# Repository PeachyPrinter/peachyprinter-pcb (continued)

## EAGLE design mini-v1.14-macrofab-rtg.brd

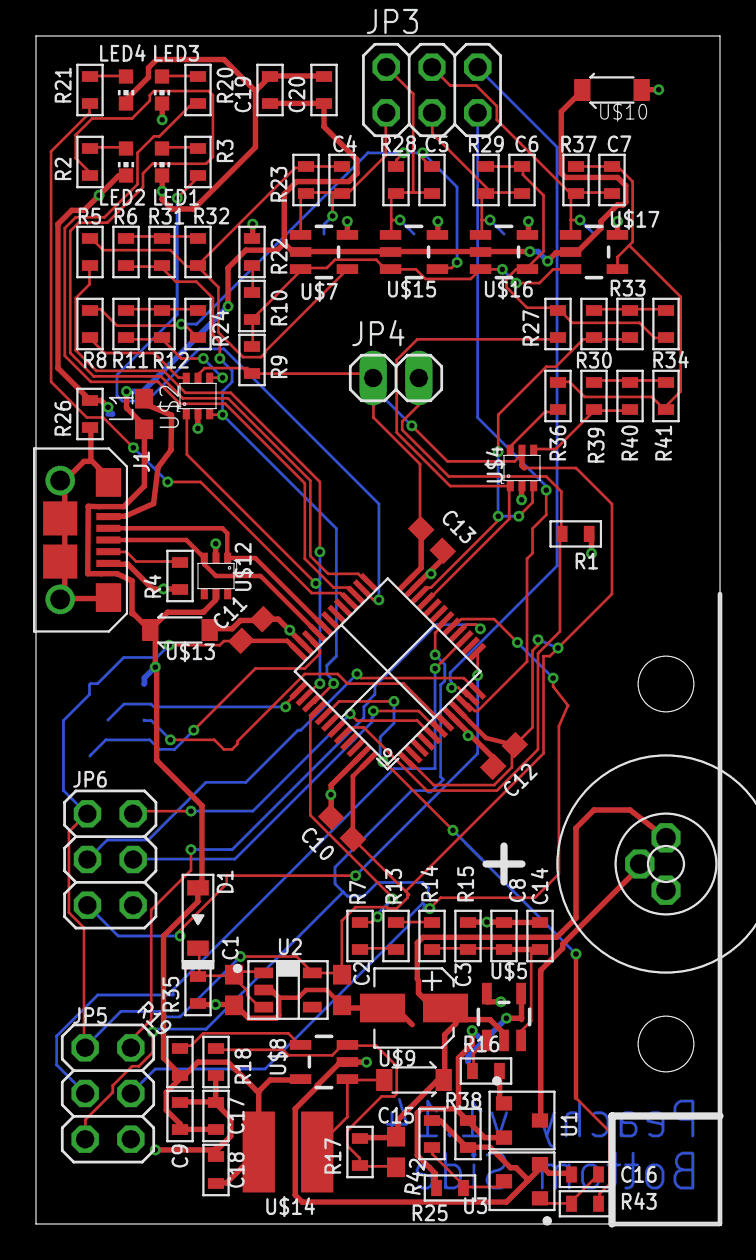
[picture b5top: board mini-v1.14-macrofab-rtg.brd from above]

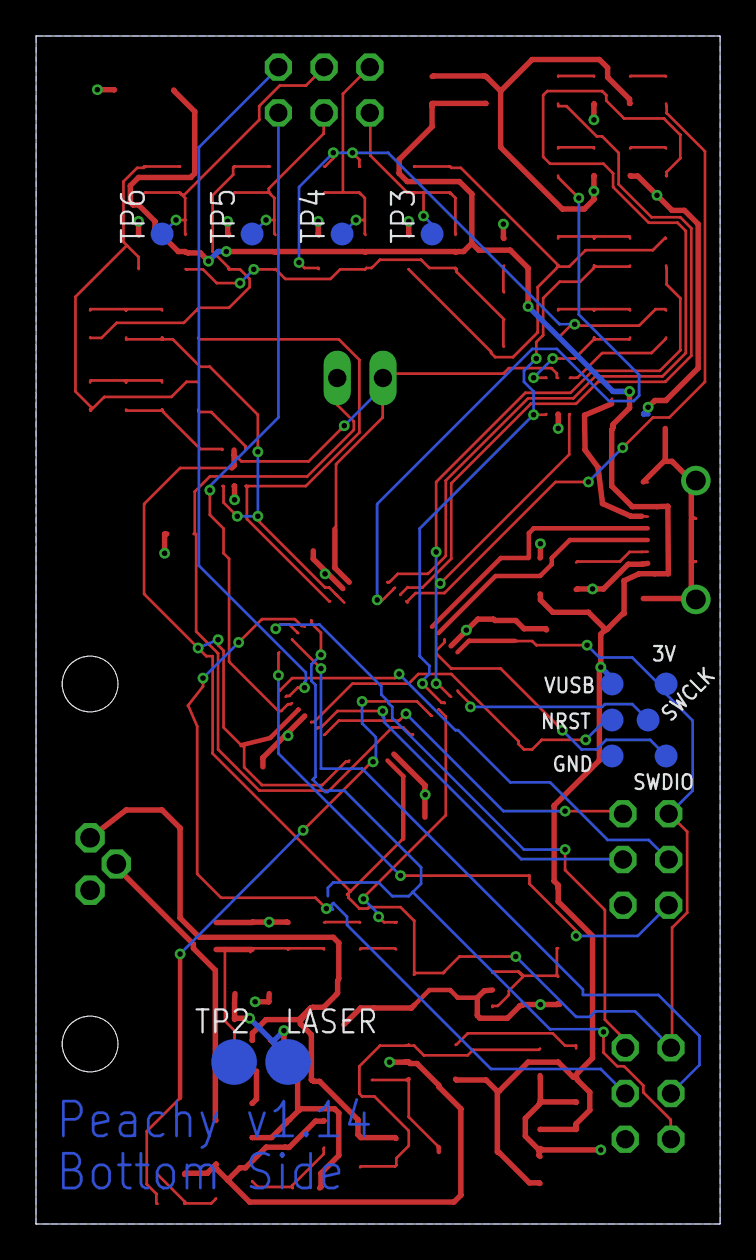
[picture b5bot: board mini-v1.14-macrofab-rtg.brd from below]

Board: 2 copper layers, 38.0 x 66.0 mm, 104 parts (12 on the bottom side), 68 nets.

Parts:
3V: TPB1,27; B1,27
C1, C2, C9, C17, C19: 1uF; C0603
C3: 10uF; CP4MM
C4, C5, C6, C7: 100n; C0603
C8, C10, C11, C12, C13, C14, C16, C18, C20: 0.1uF; C0603
C15: 560pF/50V; C0603
D1: BAT42; SOD-123
GND: TPB1,27; B1,27
J1: MICROUSB-RIGHT
JP3, JP5, JP6: 2X03
JP4: 1X02
L1: ferrite; C0603
LASER: TPB2,54; B2,54
LD1: SCOTT_LASERDIODELD3; SCOTT_LASERDIODE3
LED1, LED2, LED3, LED4: CHIP-LED0603
NRST: TPB1,27; B1,27
R1, R18: 13k3; R0603
R2, R3, R5, R7, R8, R9, R10, R20, R21, R22, R23, R27, R28, R29, R36, R37: 2k; R0603
R4: 100k; R0603
R6, R11, R12, R19, R30, R31, R33, R35, R39, R40: 825k; R0603
R13, R14, R15, R38, R43: 1k69; R0603
R16, R25: 10; R0603
R17: 63k4; R0603
R24, R26, R32, R34, R41: 604k; R0603
R42: N/C; R0603
SWCLK: TPB1,27; B1,27
SWDIO: TPB1,27; B1,27
TP2: GND; B2,54
TP3, TP4, TP5, TP6: TPB1,27; B1,27
U1, U3: BSS138; SOT-23-3
U2: TLV70233PDBVR; SOT-23-5
U$1: STM32F042C6T6-LQFP48; LQFP48
U$2, U$4: NC7WZ14P6X; SC70-6
U$5, U$7, U$15, U$16, U$17: LMC7101; SOT23-5
U$8: LMR62014; SOT23-5
U$9: MBR0520; SOD123
U$10, U$13: SMF6.0A; SOD123
U$12: SP3002-04JTG; SC70-6
U$14: SDR0403-100ML; SDR0403
VUSB: TPB1,27; B1,27

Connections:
2V2: R9.P$1, R10.P$2, U$7.3, U$15.3, U$16.3, U$17.3
3V: 3V.TP, C2.2, C10.1, C11.1, C12.1, C13.1, JP4.1, JP5.1, JP6.1, R9.P$2, U2.P$5, U$1.P1, U$1.P9, U$1.P24, U$1.P36, U$1.P48, U$2.P5, U$4.P5
6V: C3.P$1, C15.2, LD1.P$1, R17.P$2, U$5.2, U$9.CATHODE
ADC0: JP3.5, U$1.P10
ADC1: JP3.6, U$1.P11
ADC2: JP6.3, U$1.P12
ADC3: JP6.5, U$1.P13
BOOT0: JP4.2, R1.P$2, U$1.P44
COARSE1: R8.P$1, U$2.P6
FINE1: R11.P$1, R12.P$1, U$2.P4
FINE3: R39.P$1, R40.P$1, U$4.P4
GND: C1.2, C2.1, C3.P$2, C8.P$2, C9.P$2, C10.2, C11.2, C12.2, C13.2, C14.P$2, C16.P$2, C17.P$2, C18.P$2, C19.P$2, C20.P$2, GND.TP, J1.5, JP5.6, JP6.6, LED1.C, LED2.C, LED3.C, LED4.C, R1.P$1, R4.P$1, R15.P$2, R18.P$1, R22.P$1, R26.P$2, R35.P$1, R38.P$1, R42.P$1, TP2.TP, U2.P$2, U3.P$2, U$1.P8, U$1.P23, U$1.P35, U$1.P47, U$2.P2, U$4.P2, U$5.5, U$7.5, U$8.2, U$10.ANODE, U$12.P2, U$13.ANODE, U$15.5, U$16.5, U$17.5
LASER_EN: R43.P$2, U$1.P41
LASER_PWM_IN: R7.P$2, U$1.P40
MISO: JP5.2, U$1.P16
MOSI: JP5.4, U$1.P17
unnamed: R25.P$1, R42.P$2, U3.P$3
unnamed: R2.P$2, U$1.P25
unnamed: LED2.A, R2.P$1
unnamed: C1.1, D1.CATHODE, R35.P$2, U2.P$1, U2.P$3
unnamed: J1.4, R4.P$2
unnamed: R7.P$1, R13.P$2
unnamed: R36.P$1, U$4.P6
unnamed: R11.P$2, R12.P$2, R24.P$1
unnamed: R13.P$1, R14.P$2
unnamed: C5.P$1, R8.P$2, R24.P$2, R28.P$2, U$15.4
unnamed: C8.P$1, C14.P$1, R14.P$1, R15.P$1, U$5.3
unnamed: LED1.A, R3.P$1
unnamed: R3.P$2, U$1.P26
unnamed: J1.1, L1.2
unnamed: U$8.1, U$9.ANODE, U$14.P$2
unnamed: LD1.P$3, U1.P$3
unnamed: LASER.TP, R25.P$2, R38.P$2, U1.P$2, U$5.4
unnamed: J1.S1, J1.S2, J1.S3, J1.S4, J1.S5, J1.S6, R26.P$1
unnamed: R16.P$2, U1.P$1
unnamed: R16.P$1, U$5.1
unnamed: C16.P$1, R43.P$1, U3.P$1
unnamed: R10.P$1, R22.P$2
unnamed: LED3.A, R20.P$1
unnamed: C15.1, R17.P$1, R18.P$2, U$8.3
unnamed: R19.P$2, U$8.4
unnamed: LED4.A, R21.P$1
unnamed: R20.P$2, U$1.P27
unnamed: R21.P$2, U$1.P28
unnamed: R30.P$2, R33.P$2, R34.P$1
unnamed: R6.P$2, R31.P$2, R32.P$1
unnamed: C6.P$1, R27.P$2, R29.P$2, R34.P$2, U$16.4
unnamed: R39.P$2, R40.P$2, R41.P$1
unnamed: C7.P$1, R36.P$2, R37.P$2, R41.P$2, U$17.4
NRST: NRST.TP, U$1.P7
OUT: C4.P$2, JP3.1, R23.P$1, TP3.TP, U$7.1
OUT1: C5.P$2, JP3.2, R28.P$1, TP4.TP, U$15.1
OUT2: C6.P$2, JP3.3, R29.P$1, TP5.TP, U$16.1
OUT3: C7.P$2, JP3.4, R37.P$1, TP6.TP, U$17.1
SCK: JP5.3, U$1.P15
SCL: JP6.4, U$1.P6
SDA: JP6.2, U$1.P5
SPI_CS: JP5.5, U$1.P18
SWCLK: SWCLK.TP, U$1.P37
SWDIO: SWDIO.TP, U$1.P34
USB_DM: J1.2, U$1.P32, U$12.P1
USB_DP: J1.3, U$1.P33, U$12.P3
VUSB: C9.P$1, C17.P$1, C18.P$1, C19.P$1, C20.P$1, D1.ANODE, L1.1, R19.P$1, U$7.2, U$8.5, U$10.CATHODE, U$12.P5, U$13.CATHODE, U$14.P$1, U$15.2, U$16.2, U$17.2, VUSB.TP
XCOARSE_IN: R5.P$1, U$1.P38, U$2.P1
XFINE_IN: R6.P$1, R31.P$1, U$1.P39, U$2.P3
XSUM: C4.P$1, R5.P$2, R23.P$2, R32.P$2, U$7.4
YCOARSE_IN: R27.P$1, U$1.P21, U$4.P1
YFINE_IN: R30.P$1, R33.P$1, U$1.P22, U$4.P3

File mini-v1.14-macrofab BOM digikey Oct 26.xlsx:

Qty | Value | Device | DK P/N | Extended | DK for Ext$ | Package | DK Order Oct 26 | Boards Oct 26
13 | 100n | CAPACITOR_NP_0603 | 399-1095-2-ND | 65000 | 362.7 | C0603 | 4000 | 307
1 | 10uF | CAPACITOR_P_4MM | 490-7201-2-ND | 5000 | 484.35 | CP4MM | 250 | 250
5 | 1uF | C-USC0603 | 311-1443-2-ND | 25000 | 178.25 | C0603 | 4000 | 800
1 | 560pF/50V | C-USC0603 | 1276-1278-2-ND | 5000 | 62.9 | C0603 | 4000 | 4000
1 | BAT42 | DIODE_SOD-123 | BAT42W-FDITR-ND | 5000 | 442.2 | SOD-123 | 120 | 120
4 |  | LEDCHIP-LED0603 | 475-2512-2-ND | 20000 | 1071.2 | CHIP-LED0603 | 1000 | 250
5 | LMC7101 | LMC7101 | 576-2575-2-ND | 25000 | 7725.5 | SOT23-5 | 600 | 120
1 | LMR62014 | LMR62014 | 296-39046-2-ND | 5000 | 2595.5500000000002 | SOT23-5 | 120 | 120
1 | ferrite | L-US | 445-1565-2-ND | 5000 |  | C0603 | 4000 | 4000
1 | MBR0520 | MBR0520 | MBR0520LT1GOSTR-ND | 5000 | 397.2 | SOD123 | 120 | 120
2 | SMF6.0A | MBR0520 | F5749TR-ND | 10000 | 1517.1 | SOD123 | 250 | 125
2 | NC7WZ14P6X | NC7WZ14P6X | NC7WZ14P6XTR-ND | 10000 | 810.4 | SC70-6 | 250 | 125
2 | BSS138 | N-CHANNEL_FET_SOT-23-3 | BSS138LT3GOSTR-ND | 10000 | 451.64 | SOT-23-3 | 240 | 120
3 |  | PINHD-2X3 | 952-1921-ND | 15000 | 2617.5 | 2X03 | 360 | 120
2 | 10 | RESISTOR_0603 | 311-10.0HRTR-ND | 10000 | 21.26 | R0603 | 5000 | 2500
1 | 100k | RESISTOR_0603 | 311-100KHRTR-ND | 5000 | 9.6199999999999992 | R0603 | 5000 | 5000
2 | 13k3 | RESISTOR_0603 | 311-13.3KHRTR-ND | 10000 | 21.26 | R0603 | 5000 | 2500
5 | 1k69 | RESISTOR_0603 | 311-1.69KHRTR-ND | 25000 | 47.5 | R0603 | 5000 | 1000
16 | 2k | RESISTOR_0603 | 311-2.00KHRTR-ND | 80000 | 139.19999999999999 | R0603 | 5000 | 312
5 | 604k | RESISTOR_0603 | 311-604KHRTR-ND | 25000 | 47.5 | R0603 | 5000 | 1000
1 | 63k4 | RESISTOR_0603 | 311-63.4KHRTR-ND | 5000 | 12.45 | R0603 | 5000 | 5000
10 | 825k | RESISTOR_0603 | 311-825KHRTR-ND | 50000 | 21.62 | R0603 | 5000 | 500
1 | SDR0403-100ML | SDR0403 | SDR0403-100MLTR-ND | 5000 | 1287.25 | SDR0403 | 120 | 120
1 | SP3002-04JTG | SP3002 | F2916TR-ND | 5000 | 1824.75 | SC70-6 | 120 | 120
1 | STM32F070CBT6 | STM32F042-LQFP48 | 497-15099-ND | 5000 | 8179.93 | LQFP48 | 120 | 120
1 | TLV70233PDBVR | TLV70233PDBVR | 296-39284-2-ND | 5000 | 767.64 | SOT-23-5 | 120 | 120
1 |  | USB_MICRO_RIGHT | 609-4618-2-ND | 5000 | 1258.45 | MICROUSB-RIGHT | 120 | 120
TOTAL |  |  |  |  | 32354.92 |  |  | 120 | 16.366666666666667
PER BOARD |  |  |  |  | 6.4709839999999996

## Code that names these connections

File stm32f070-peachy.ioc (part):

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Mcu.Name=STM32F070CBTx
Mcu.Package=LQFP48
Mcu.UserName=STM32F070CBTx
PA0.Mode=IN0
PA0.Signal=ADC_IN0
PA1.Mode=IN1
PA1.Signal=ADC_IN1
PA11.Mode=Device
PA11.Signal=USB_DM
PA12.Mode=Device
PA12.Signal=USB_DP
PA13.Mode=Serial-WireDebug
PA13.Signal=SYS_SWDIO
PA14.Mode=Serial-WireDebug
PA14.Signal=SYS_SWCLK
PA2.Mode=IN2
PA2.Signal=ADC_IN2
PA3.Mode=IN3
PA3.Signal=ADC_IN3
PA4.GPIOParameters=GPIO_Label
PA4.GPIO_Label=SPI_CS
PA4.Signal=GPIO_Output
PA5.Mode=Full_Duplex_Master
PA5.Signal=SPI1_SCK
PA6.Mode=Full_Duplex_Master
PA6.Signal=SPI1_MISO
PA7.Mode=Full_Duplex_Master
PA7.Signal=SPI1_MOSI
PB0.GPIOParameters=GPIO_Label
PB0.GPIO_Label=YCOARSE_IN
PB0.Signal=S_TIM3_CH3
PB1.GPIOParameters=GPIO_Label
PB1.GPIO_Label=YFINE_IN
PB1.Signal=S_TIM3_CH4
PB10.Mode=I2C
PB10.Signal=I2C2_SCL
PB11.Mode=I2C
PB11.Signal=I2C2_SDA
PB14.GPIOParameters=GPIO_Label
PB14.GPIO_Label=LASER_PWM_IN
PB14.Signal=S_TIM15_CH1
PB15.GPIOParameters=GPIO_Label
PB15.GPIO_Label=LASER_EN
PB15.Signal=GPIO_Output
PB4.GPIOParameters=GPIO_Label
PB4.GPIO_Label=XCOARSE_IN
PB4.Signal=S_TIM3_CH1
PB5.GPIOParameters=GPIO_Label
PB5.GPIO_Label=XFINE_IN
PB5.Signal=S_TIM3_CH2
board=custom

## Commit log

2016-05-12 adding the other files that werent part of the original commit - enjoy!
2016-05-12 adding readme
